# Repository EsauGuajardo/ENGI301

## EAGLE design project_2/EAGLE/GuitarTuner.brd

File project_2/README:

This project was to design a PCB for the device we created for project #1. I created a PCB of a guitar tuner, which is able to register the sounds coming from the string of a guitar and reply whether it is sharp or flat. Included in this project folder are the three eagle files (schematic, board, and library) along with a bill of materials file.

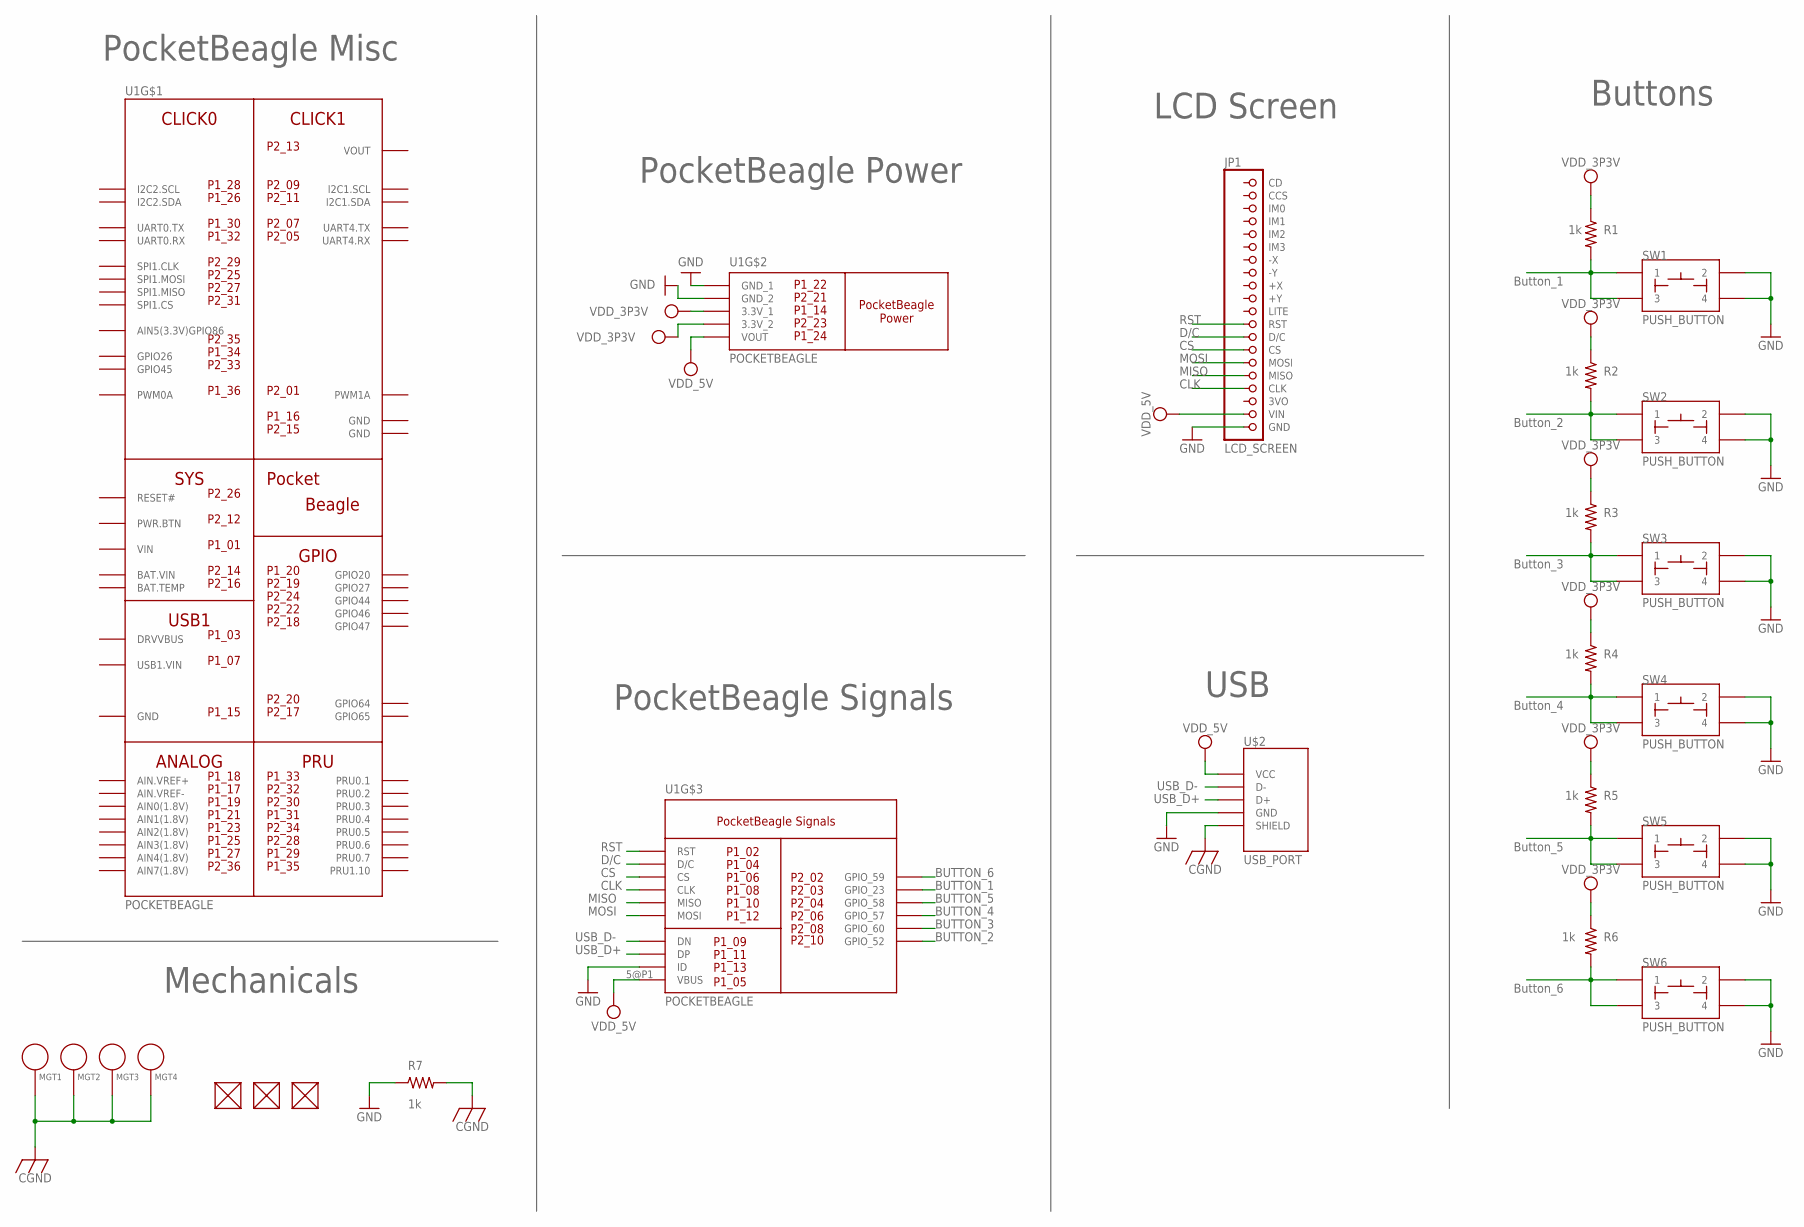
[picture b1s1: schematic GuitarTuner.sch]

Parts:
FUD1, FUD2, FUD3: FIDUCIAL; FIDUCIAL_40MIL
JP1: LCD_SCREEN; 1X20_ROUND
MGT1, MGT2, MGT3, MGT4: MOUNTING_HOLE
R1, R2, R3, R4, R5, R6: 1k; R0603
R7: 1k; R0805
SW1, SW2, SW3, SW4, SW5, SW6: PUSH_BUTTON; BUTTON_12.5MM
U1: POCKETBEAGLE
U$2: USB_PORT

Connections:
BAT.VIN: U1.14@P2 (BAT.VIN)
BUTTON_1: R1.2, SW1.1, SW1.3, U1.3@P2 (GPIO_23)
BUTTON_2: R2.2, SW2.1, SW2.3, U1.10@P2 (GPIO_52)
BUTTON_3: R3.2, SW3.1, SW3.3, U1.8@P2 (GPIO_60)
BUTTON_4: R4.2, SW4.1, SW4.3, U1.6@P2 (GPIO_57)
BUTTON_5: R5.2, SW5.1, SW5.3, U1.4@P2 (GPIO_58)
BUTTON_6: R6.2, SW6.1, SW6.3, U1.2@P2 (GPIO_59)
CGND: MGT1.P$1, MGT2.P$1, MGT3.P$1, MGT4.P$1, R7.2, U$2.SH1 (SHIELD); also elsewhere on the board
CLK: JP1.17 (CLK), U1.8@P1 (CLK)
CS: JP1.14 (CS), U1.6@P1 (CS)
D/C: JP1.13 (D/C), U1.4@P1 (D/C)
GND: JP1.20 (GND), R7.1, SW1.2, SW1.4, SW2.2, SW2.4, SW3.2, SW3.4, SW4.2, SW4.4, SW5.2, SW5.4, SW6.2, SW6.4, U1.13@P1 (ID), U1.15@P2 (GND), U1.16@P1 (GND), U1.21@P2 (GND_2), U1.22@P1 (GND_1), U$2.4 (GND); also elsewhere on the board
MISO: JP1.16 (MISO), U1.10@P1 (MISO)
MOSI: JP1.15 (MOSI), U1.12@P1 (MOSI)
RST: JP1.12 (RST), U1.1@P2 (RST)
USB_D+: U1.11@P1 (DP), U$2.3 (D+); also elsewhere on the board
USB_D-: U1.9@P1 (DN), U$2.2 (D-); also elsewhere on the board
VDD_3P3V: R1.1, R2.1, R3.1, R4.1, R5.1, R6.1, U1.14@P1 (3.3V_1), U1.23@P2 (3.3V_2)
VDD_5V: JP1.19 (VIN), U1.5@P1 (VBUS), U1.24@P1 (VOUT), U$2.1 (VCC); also elsewhere on the board
VIN: U1.2@P1 (VIN)
VOUT: U1.13@P2 (VOUT)

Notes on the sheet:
Button_1
Button_2
Button_3
Button_4
Button_5
Button_6
PocketBeagle Misc
PocketBeagle Power
PocketBeagle Signals
USB
LCD Screen
Buttons
USB_D-
USB_D+
Mechanicals

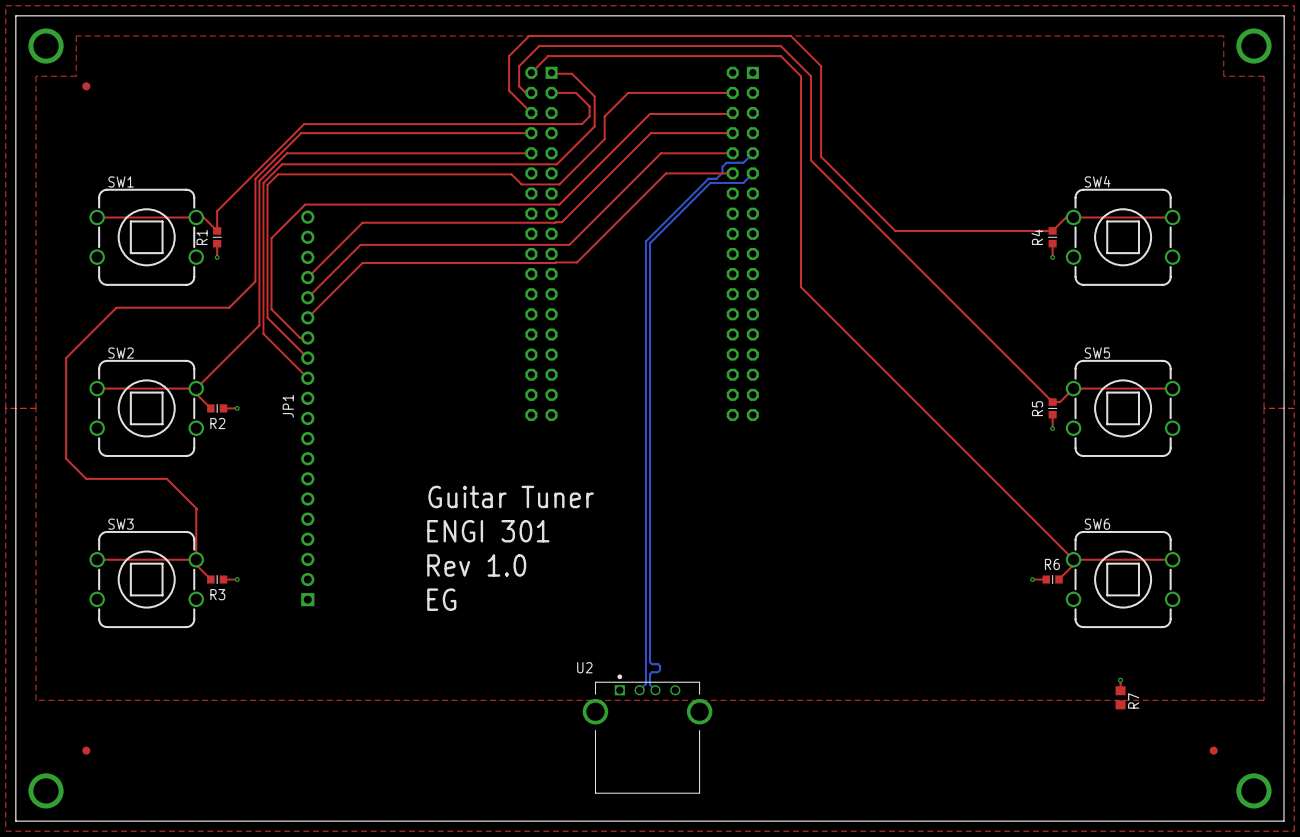
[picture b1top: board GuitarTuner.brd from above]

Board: 4 copper layers, 160.0 x 101.6 mm, 23 parts (1 on the bottom side), 18 nets.

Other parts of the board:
U2: USB_PORT

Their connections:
CGND: U2.SH1, U2.SH2; also elsewhere on the board
GND: U2.4; also elsewhere on the board
USB_D+: U2.3; also elsewhere on the board
USB_D-: U2.2; also elsewhere on the board
VDD_5V: U2.1; also elsewhere on the board

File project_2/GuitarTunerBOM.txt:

Qty Value         Device           Package        Parts                        Description                                    
6   1k            R_R0603          R0603          R1, R2, R3, R4, R5, R6       RESISTOR, American symbol                      
1   1k            R_R0805          R0805          R7                           RESISTOR, American symbol                      
3   FIDUCIAL      FIDUCIAL         FIDUCIAL_40MIL FUD1, FUD2, FUD3                                                            
1   LCD_SCREEN    HEADER-1X20ROUND 1X20_ROUND     JP1                                                                         
4   MOUNTING_HOLE MOUNTING_HOLE    MOUNTING_HOLE  MGT1, MGT2, MGT3, MGT4       Chassis Mounting Hole w/GND connection ability 
1   POCKETBEAGLE  POCKETBEAGLE     POCKETBEAGLE   U1                                                                          
6   PUSH_BUTTON   PUSH_BUTTON      BUTTON_12.5MM  SW1, SW2, SW3, SW4, SW5, SW6                                                
1   USB_PORT      USB_PORT         USB_PORT       U$2

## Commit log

2022-02-01 Updating README.md
2022-02-16 commit1
2022-02-24 commit2
2022-04-05 adding files
2022-05-04 Create gitkeep
2022-05-04 Create asdf
2022-05-04 Rename project_2/GuitarTuner.brd to project_2/EAGLE/GuitarTuner.brd
2022-05-04 Rename project_2/GuitarTuner.lbr to project_2/EAGLE/GuitarTuner.lbr
2022-05-04 Rename project_2/GuitarTuner.sch to project_2/EAGLE/GuitarTuner.sch
